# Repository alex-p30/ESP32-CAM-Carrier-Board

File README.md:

# ESP32-CAM-Carrier-Board
WLED Carrier board for the ESP32-CAM by AI-Thinker.
More details: https://alexpizzi.me/my-big-led-array

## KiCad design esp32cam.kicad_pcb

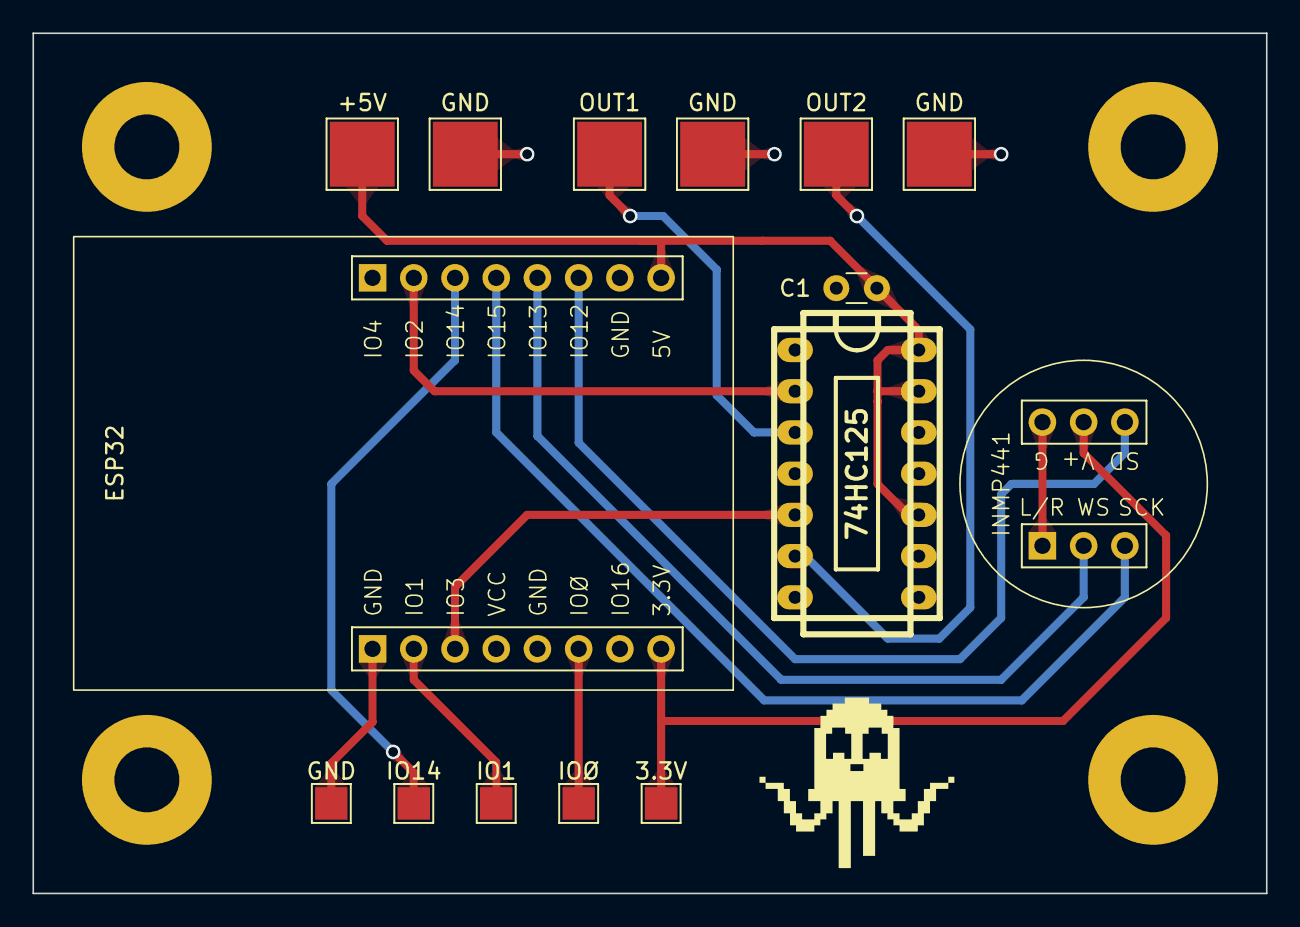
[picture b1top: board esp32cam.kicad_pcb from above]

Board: 2 copper layers, 76.0 x 53.0 mm, 19 parts (0 on the bottom side), 13 nets.

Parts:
3.3V: IO0; TestPoint_Pad_2.0x2.0mm
74HC125: 74HC125; dil_14-300_socket
+5V: 5V; TestPoint_Pad_4.0x4.0mm
C1: 0.1uF; C_Disc_D3.0mm_W1.6mm_P2.50mm
ESP32: ESP32; ESP32-CAM
GND: GND; TestPoint_Pad_4.0x4.0mm
GND#2, GND#4: GND; TestPoint_Pad_4.0x4.0mm
GND#3: GND; TestPoint_Pad_2.0x2.0mm
H1, H2, H3, H4: MountingHole; MountingHole_4mm_Pad
INMP441: INMP441; INMP441-SOCKET
IO1: IO1; TestPoint_Pad_2.0x2.0mm
IO14: IO14; TestPoint_Pad_2.0x2.0mm
IOØ: IO0; TestPoint_Pad_2.0x2.0mm
OUT1: OUT1; TestPoint_Pad_4.0x4.0mm
OUT2: OUT2; TestPoint_Pad_4.0x4.0mm

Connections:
+3.3V: 3.3V.1, ESP32.8 (3.3V), INMP441.5 (VDD)
+5V: 74HC125.10, 74HC125.13, 74HC125.14, +5V.1, C1.1, ESP32.9 (5V)
GND: 74HC125.1, 74HC125.4, 74HC125.7, 74HC125.9, 74HC125.12, C1.2, ESP32.1 (GND), ESP32.5 (GND), ESP32.10 (GND), GND.1, GND#2.1, GND#3.1, GND#4.1, INMP441.1 (L/R), INMP441.6 (GND)
IO0: ESP32.6 (IO0), IOØ.1
IO1: ESP32.2 (IO1), IO1.1
IO2: 74HC125.2, ESP32.15 (IO2)
IO3: 74HC125.5, ESP32.3 (IO3)
IO12: ESP32.11 (IO12), INMP441.4 (SD)
IO13: ESP32.12 (IO13), INMP441.2 (WS)
IO14: ESP32.14 (IO14), IO14.1
IO15: ESP32.13 (IO15), INMP441.3 (SCK)
OUT1: 74HC125.3, OUT1.1
OUT2: 74HC125.6, OUT2.1
